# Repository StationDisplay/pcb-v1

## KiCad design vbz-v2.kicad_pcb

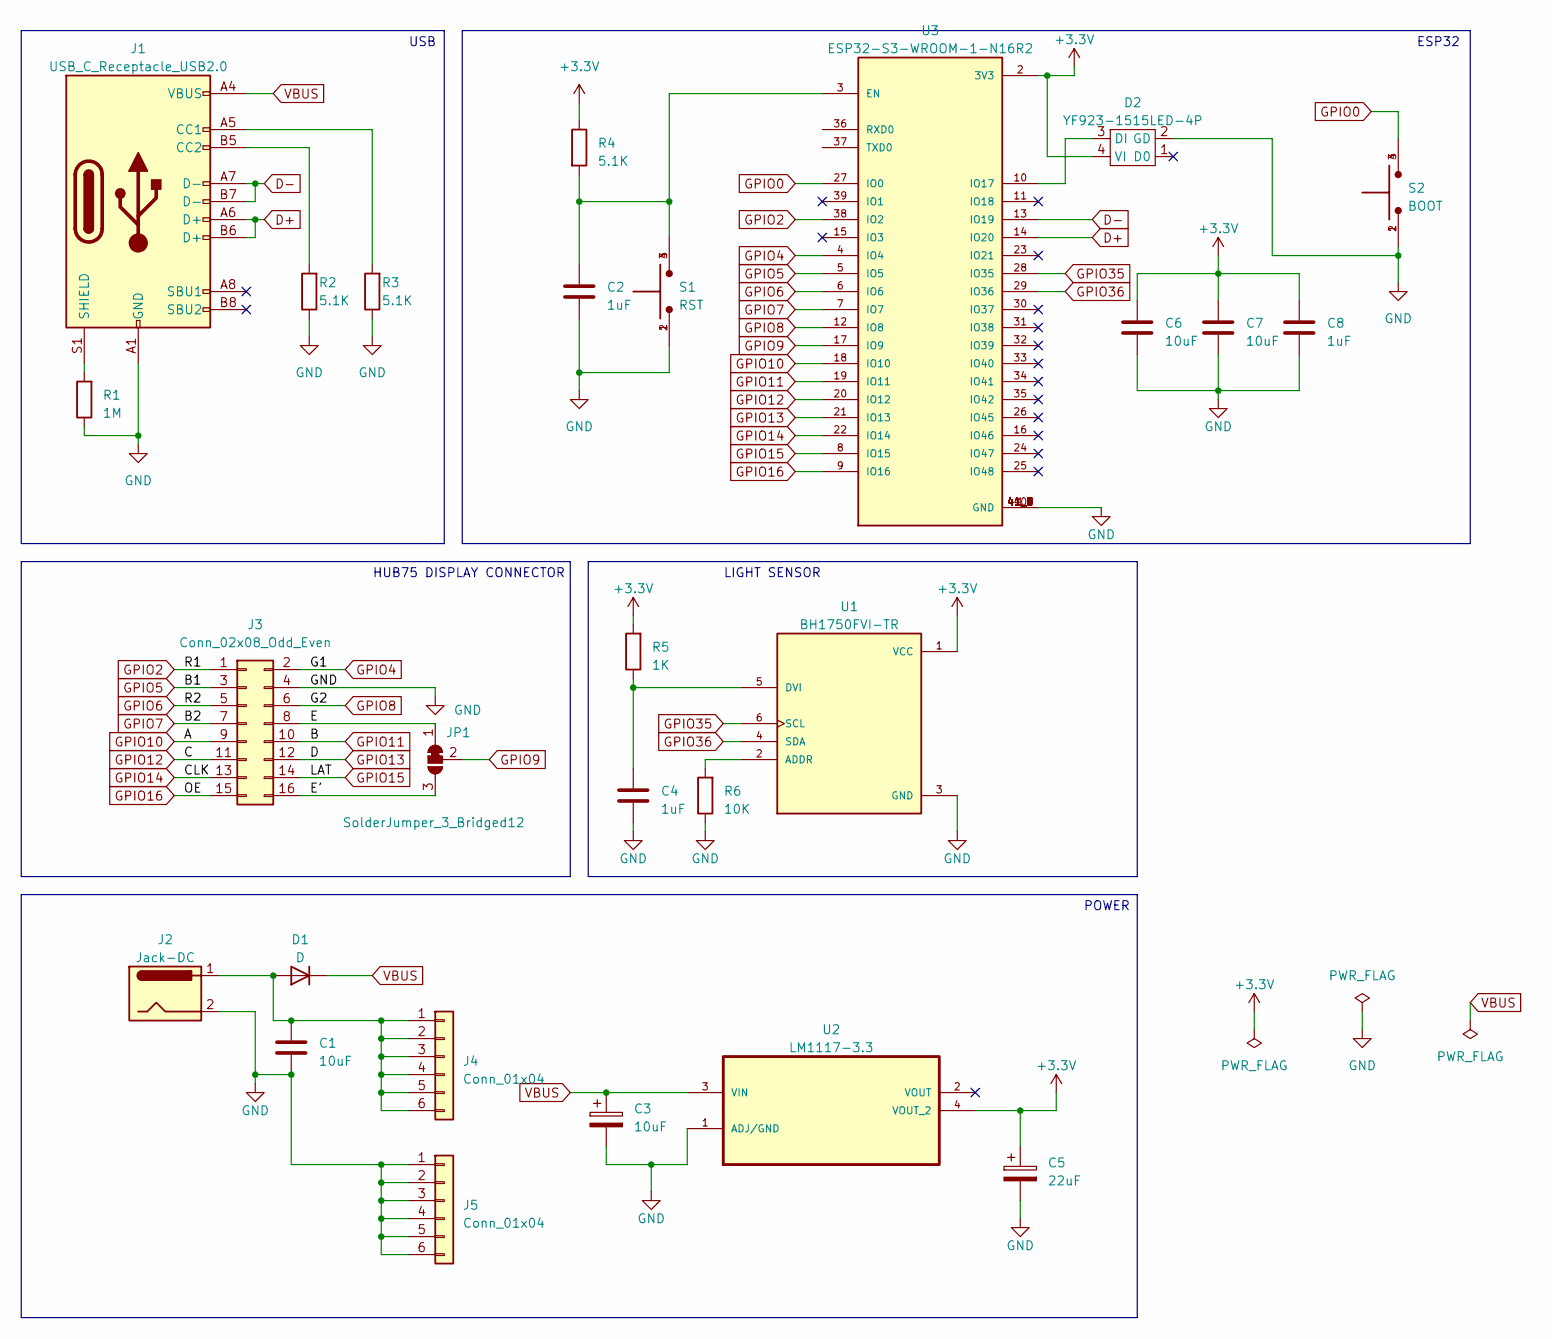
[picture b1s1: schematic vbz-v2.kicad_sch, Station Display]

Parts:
C1: 10uF; C_1825_4564Metric; LCSC C1021605
C2, C4, C8: 1uF; C_1206_3216Metric; LCSC C282823
C3: 10uF; CP_EIA-3528-12_Kemet-T; LCSC C2156473
C5: 22uF; CP_EIA-3528-12_Kemet-T; LCSC C1952922
C6, C7: 10uF; C_1206_3216Metric; LCSC C9807
D1: D; D_1206_3216Metric; LCSC C143805
D2: YF923-1515LED-4P; LED_SK6812_EC15_1.5x1.5mm; LCSC C5349954
J1: USB_C_Receptacle_USB2.0; TYPE-C-31-M-14; LCSC C223907
J2: Jack-DC; BarrelJack_Kycon_KLDX-0202-xC_Horizontal; LCSC C111573
J3: Conn_02x08_Odd_Even; IDC-Header_2x08_P2.54mm_Vertical_SMD; LCSC C601969
J4, J5: Conn_01x04; JST_VH_B6P-VH-B_1x06_P3.96mm_Vertical; LCSC C160314
JP1: SolderJumper_3_Bridged12; SolderJumper-3_P1.3mm_Bridged12_RoundedPad1.0x1.5mm
R1: 1M; R_1206_3216Metric; LCSC C104604
R2, R3, R4: 5.1K; R_1206_3216Metric; LCSC C17968
R5: 1K; R_1206_3216Metric; LCSC C4410
R6: 10K; R_1206_3216Metric; LCSC C17902
S1: RST; SW_SKRPABE010; LCSC C115360
S2: BOOT; SW_SKRPABE010; LCSC C115360
U1: BH1750FVI-TR; XDCR_BH1750FVI-TR; PARTREV D; LCSC C78960
U2: LM1117-3.3; TO-263-3_TabPin4; LCSC C498315
U3: ESP32-S3-WROOM-1-N16R2; XCVR_ESP32-S3-WROOM-1-N16R2; PARTREV v1.0; LCSC C2913198

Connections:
+3.3V: C5.1, C6.1, C7.1, C8.1, D2.4 (VI), R4.1, R5.2, U1.1 (VCC), U2.4 (VOUT_2), U3.2 (3V3)
/E: J3.8, JP1.1 (A)
/E': J3.16, JP1.3 (B)
D+: J1.A6 (D+), J1.B6 (D+), U3.14 (IO20)
D-: J1.A7 (D-), J1.B7 (D-), U3.13 (IO19)
GND: C1.2, C2.2, C3.2, C4.2, C5.2, C6.2, C7.2, C8.2, D2.2 (GD), J1.A1 (GND), J1.A12 (GND), J1.B1 (GND), J1.B12 (GND), J2.2, J3.4, J5.1, J5.2, J5.3, J5.4, J5.5, J5.6, R1.1, R2.1, R3.1, R6.1, S1.1, S1.2, S2.1, S2.2, U1.3 (GND), U2.1 (ADJ/GND), U3.1 (GND), U3.40 (GND), U3.41_1 (GND), U3.41_2 (GND), U3.41_3 (GND), U3.41_4 (GND), U3.41_5 (GND), U3.41_6 (GND), U3.41_7 (GND), U3.41_8 (GND), U3.41_9 (GND)
GPIO0: S2.3, S2.4, U3.27 (IO0)
GPIO2: J3.1, U3.38 (IO2)
GPIO4: J3.2, U3.4 (IO4)
GPIO5: J3.3, U3.5 (IO5)
GPIO6: J3.5, U3.6 (IO6)
GPIO7: J3.7, U3.7 (IO7)
GPIO8: J3.6, U3.12 (IO8)
GPIO9: JP1.2 (C), U3.17 (IO9)
GPIO10: J3.9, U3.18 (IO10)
GPIO11: J3.10, U3.19 (IO11)
GPIO12: J3.11, U3.20 (IO12)
GPIO13: J3.12, U3.21 (IO13)
GPIO14: J3.13, U3.22 (IO14)
GPIO15: J3.14, U3.8 (IO15)
GPIO16: J3.15, U3.9 (IO16)
GPIO35: U1.6 (SCL), U3.28 (IO35)
GPIO36: U1.4 (SDA), U3.29 (IO36)
unnamed: C1.1, D1.2 (A), J2.1, J4.1, J4.2, J4.3, J4.4, J4.5, J4.6
unnamed: D2.3 (DI), U3.10 (IO17)
unnamed: J1.A5 (CC1), R3.2
unnamed: J1.B5 (CC2), R2.2
unnamed: J1.S1 (SHIELD), R1.2
unnamed: R6.2, U1.2 (ADDR)
unnamed: C4.1, R5.1, U1.5 (DVI)
unnamed: C2.1, R4.2, S1.3, S1.4, U3.3 (EN)
VBUS: C3.1, D1.1 (K), J1.A4 (VBUS), J1.A9 (VBUS), J1.B4 (VBUS), J1.B9 (VBUS), U2.3 (VIN)

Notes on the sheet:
USB
HUB75 DISPLAY CONNECTOR
ESP32
POWER
LIGHT SENSOR

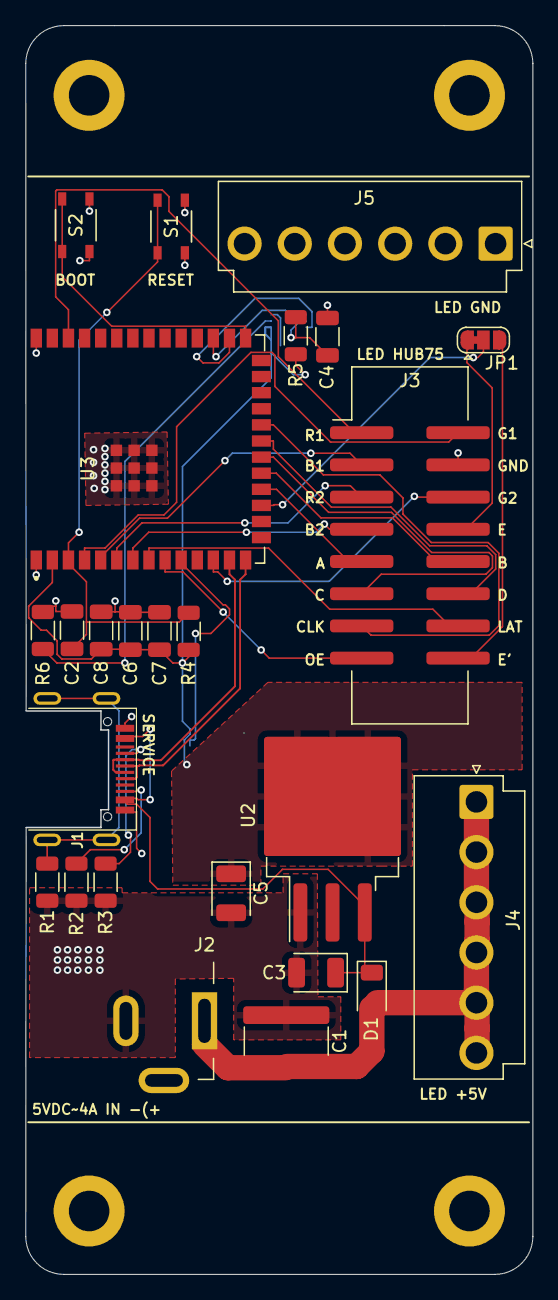
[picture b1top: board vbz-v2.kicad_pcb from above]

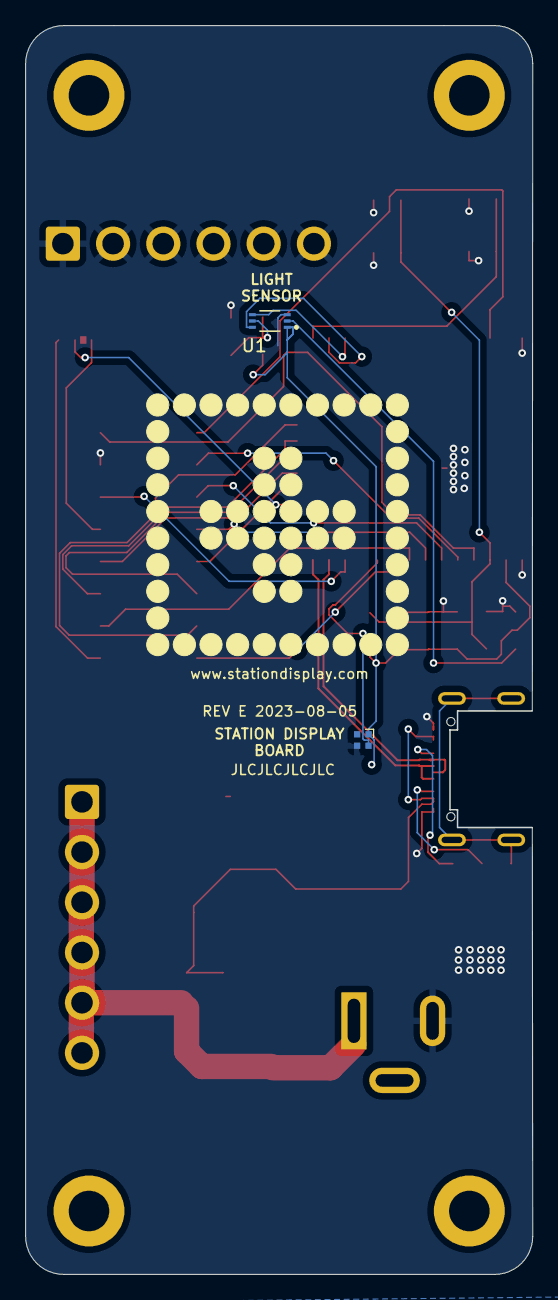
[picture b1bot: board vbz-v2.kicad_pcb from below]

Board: 2 copper layers, 39.9 x 98.4 mm, 31 parts (2 on the bottom side), 32 nets.

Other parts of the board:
H1, H2, H3, H4: MountingHole_3.2mm_M3_DIN965_Pad

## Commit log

2023-12-03 Init
